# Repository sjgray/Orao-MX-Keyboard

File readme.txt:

Orao 2007 MX Keyboard - By Walter Miraglia and Steve Gray
=====================   Updated: 2026-05-05

This is a mechanical keyboard for the Orao 2007 computer.
It is based on the original keyboard but is slightly modified.

The changes are:

- Larger SHIFT keys.
- Larger ENTER key.
- Relocated cursor/arrow keys with Inverted-T configuration.
- Relocated and re-arranged PF keys.
- 6.25U SPACEBAR, 1.5U ENTER and SHIFT keys.

MX Switches
-----------

This design takes standard MX 3-pin or 5-pin cherry-type switches.
Five-pin switches are recommended for easier alignment.

Keycaps
-------

As this layout is unique I suggest you get blank DSA or XDA keycaps
and use sticker or waterslide sheets to label the keys. There are two
Keycap Sheets; One for Light keycaps (White, Grey,Beige etc) and one
for Black keycaps. The original keyboard was used as a guide and
additional alternate labels are included such as the PF key's actual
functions, longer names for some keys, and alternate cursor arrows.

For Light keycaps I suggest using Water-slide sheets (aka decal sheets).
For Black keycaps you can use full-page sticker sheets.

Connection
----------

For Rev 1 you will need a 16-pin ribbon cable to connect to the computer pcb.
The DIP connector matches the IC socket on the Orao PCB. Rev 2 and 2b can
also use an IDC or straight Dupont connector.

 The Dupont connector can be a 90 degree header installed on either the top
or bottom of the PCB. For Dupont cables you should use the square-pin male
headers on the Orao PCB. For the IDC connecter, I have seen pre-made
IDC to DIP ribbon cables on AliExpress.

History
-------

2026-04-10 - Rev 1 - Prototype. PCB's made. Needs fixes for function keys and SPACEBAR.
2026-04-30 - Rev 2 - Fix for Function key routing, SPACEBAR position, board size reduced. Add IDC and Dupont cable options.
2026-05-02 - Rev 2b- Revert to original size pcb. This revision is recommended for Walter's 3D case design.
2026-05-05 - Add Keycap Sheets

Steve

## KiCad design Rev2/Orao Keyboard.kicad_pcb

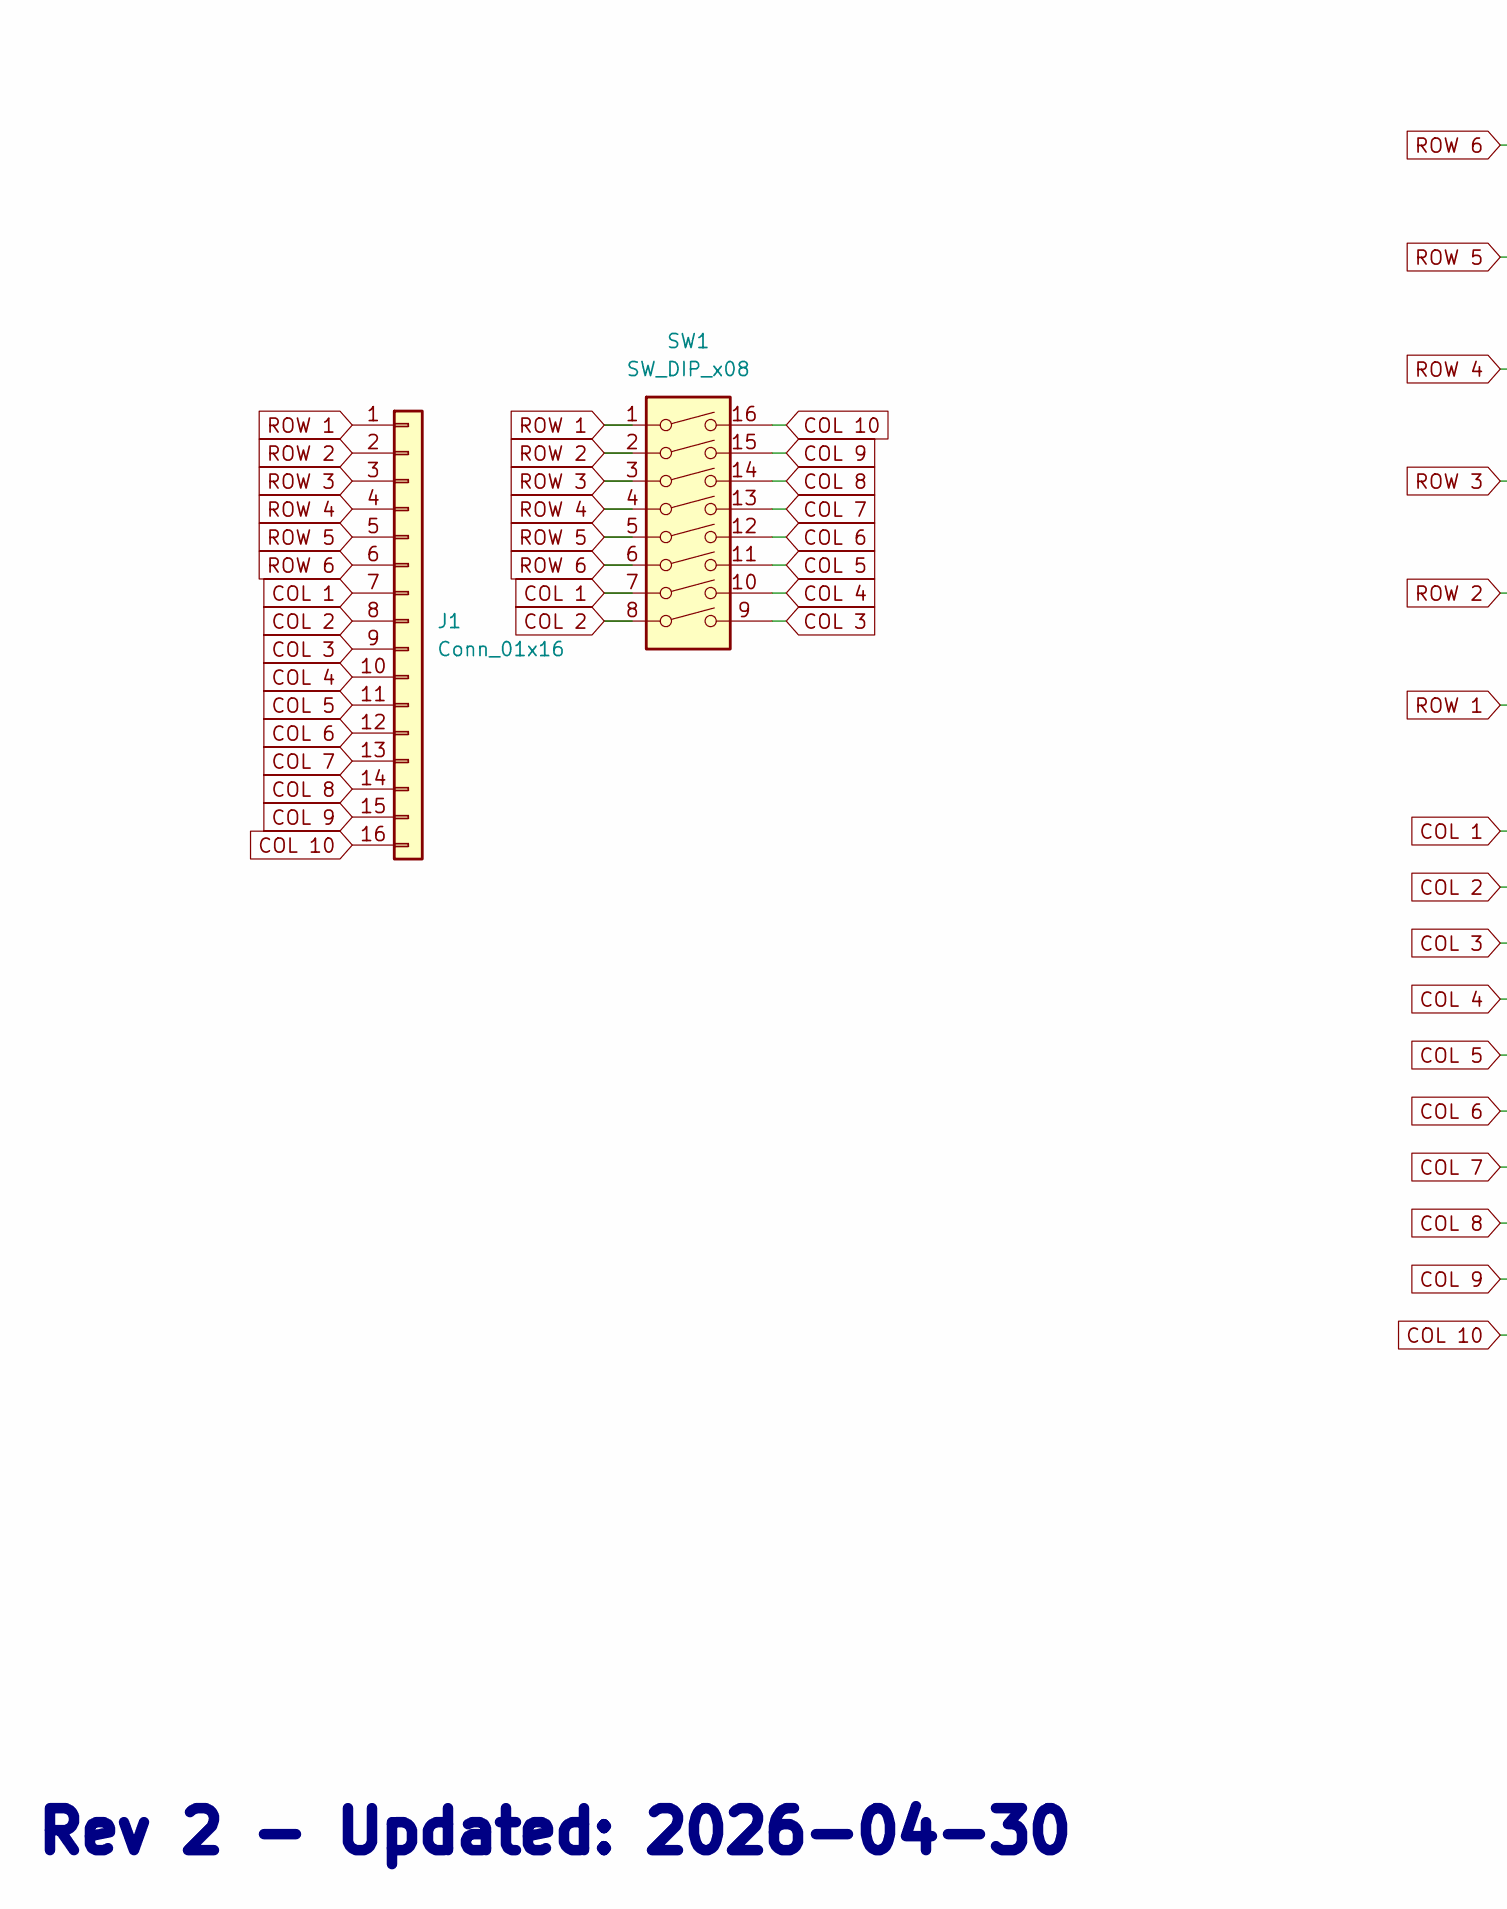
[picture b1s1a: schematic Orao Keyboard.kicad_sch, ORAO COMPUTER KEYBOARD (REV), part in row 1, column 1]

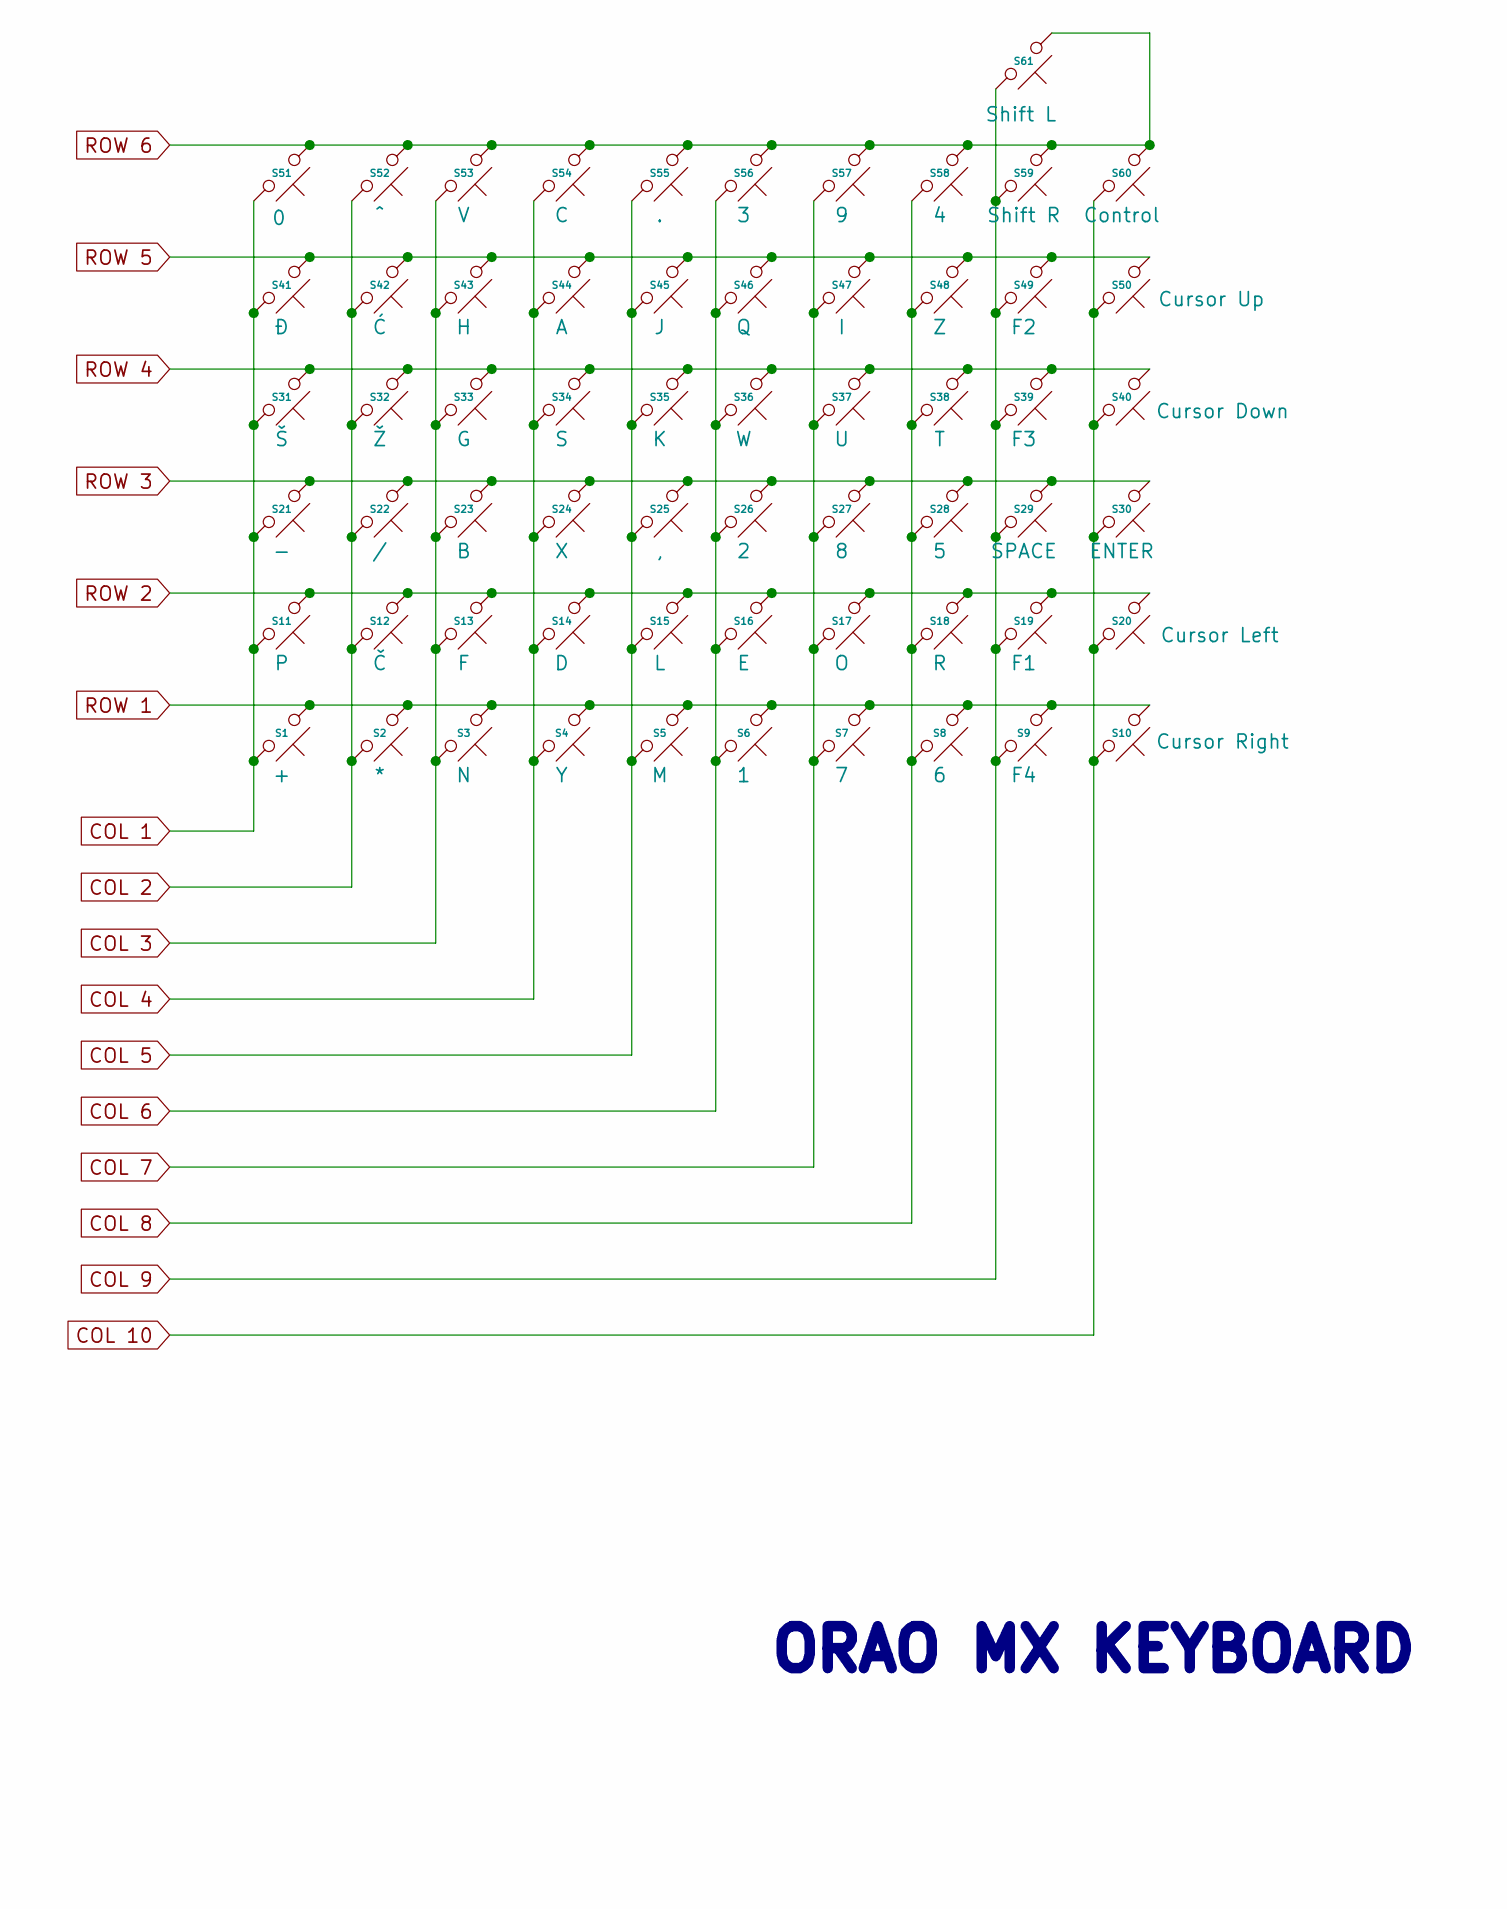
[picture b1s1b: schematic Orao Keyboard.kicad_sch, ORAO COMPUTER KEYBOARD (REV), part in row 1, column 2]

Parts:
J1: Conn_01x16; PinHeader_1x16_P2.54mm_Vertical
S1: +; MX_PCB_1.00u
S2: *; MX_PCB_1.00u
S3: N; MX_PCB_1.00u
S4: Y; MX_PCB_1.00u
S5: M; MX_PCB_1.00u
S6: 1; MX_PCB_1.00u
S7: 7; MX_PCB_1.00u
S8: 6; MX_PCB_1.00u
S9: F4; MX_PCB_1.00u
S10: Cursor Right; MX_PCB_1.00u
S11: P; MX_PCB_1.00u
S12: Č; MX_PCB_1.00u
S13: F; MX_PCB_1.00u
S14: D; MX_PCB_1.00u
S15: L; MX_PCB_1.00u
S16: E; MX_PCB_1.00u
S17: O; MX_PCB_1.00u
S18: R; MX_PCB_1.00u
S19: F1; MX_PCB_1.00u
S20: Cursor Left; MX_PCB_1.00u
S21: -; MX_PCB_1.00u
S22: /; MX_PCB_1.00u
S23: B; MX_PCB_1.00u
S24: X; MX_PCB_1.00u
S25: ,; MX_PCB_1.00u
S26: 2; MX_PCB_1.00u
S27: 8; MX_PCB_1.00u
S28: 5; MX_PCB_1.00u
S29: SPACE; MX_PCB_6.25u
S30: ENTER; MX_PCB_1.50u
S31: Š; MX_PCB_1.00u
S32: Ž; MX_PCB_1.00u
S33: G; MX_PCB_1.00u
S34: S; MX_PCB_1.00u
S35: K; MX_PCB_1.00u
S36: W; MX_PCB_1.00u
S37: U; MX_PCB_1.00u
S38: T; MX_PCB_1.00u
S39: F3; MX_PCB_1.00u
S40: Cursor Down; MX_PCB_1.00u
S41: Đ; MX_PCB_1.00u
S42: Ć; MX_PCB_1.00u
S43: H; MX_PCB_1.00u
S44: A; MX_PCB_1.00u
S45: J; MX_PCB_1.00u
S46: Q; MX_PCB_1.00u
S47: I; MX_PCB_1.00u
S48: Z; MX_PCB_1.00u
S49: F2; MX_PCB_1.00u
S50: Cursor Up; MX_PCB_1.00u
S51: 0; MX_PCB_1.00u
S52: ^; MX_PCB_1.00u
S53: V; MX_PCB_1.00u
S54: C; MX_PCB_1.00u
S55: .; MX_PCB_1.00u
S56: 3; MX_PCB_1.00u
S57: 9; MX_PCB_1.00u
S58: 4; MX_PCB_1.00u
S59: Shift R; MX_PCB_1.50u
S60: Control; MX_PCB_1.00u
S61: Shift L; MX_PCB_1.50u
SW1: SW_DIP_x08; CERDIP-16_W7.62mm_SideBrazed_LongPads

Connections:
COL 1: J1.7, S1.1, S11.1, S21.1, S31.1, S41.1, S51.1, SW1.7
COL 2: J1.8, S2.1, S12.1, S22.1, S32.1, S42.1, S52.1, SW1.8
COL 3: J1.9, S3.1, S13.1, S23.1, S33.1, S43.1, S53.1, SW1.9
COL 4: J1.10, S4.1, S14.1, S24.1, S34.1, S44.1, S54.1, SW1.10
COL 5: J1.11, S5.1, S15.1, S25.1, S35.1, S45.1, S55.1, SW1.11
COL 6: J1.12, S6.1, S16.1, S26.1, S36.1, S46.1, S56.1, SW1.12
COL 7: J1.13, S7.1, S17.1, S27.1, S37.1, S47.1, S57.1, SW1.13
COL 8: J1.14, S8.1, S18.1, S28.1, S38.1, S48.1, S58.1, SW1.14
COL 9: J1.15, S9.1, S19.1, S29.1, S39.1, S49.1, S59.1, S61.1, SW1.15
COL 10: J1.16, S10.1, S20.1, S30.1, S40.1, S50.1, S60.1, SW1.16
ROW 1: J1.1, S1.2, S2.2, S3.2, S4.2, S5.2, S6.2, S7.2, S8.2, S9.2, S10.2, SW1.1
ROW 2: J1.2, S11.2, S12.2, S13.2, S14.2, S15.2, S16.2, S17.2, S18.2, S19.2, S20.2, SW1.2
ROW 3: J1.3, S21.2, S22.2, S23.2, S24.2, S25.2, S26.2, S27.2, S28.2, S29.2, S30.2, SW1.3
ROW 4: J1.4, S31.2, S32.2, S33.2, S34.2, S35.2, S36.2, S37.2, S38.2, S39.2, S40.2, SW1.4
ROW 5: J1.5, S41.2, S42.2, S43.2, S44.2, S45.2, S46.2, S47.2, S48.2, S49.2, S50.2, SW1.5
ROW 6: J1.6, S51.2, S52.2, S53.2, S54.2, S55.2, S56.2, S57.2, S58.2, S59.2, S60.2, S61.2, SW1.6

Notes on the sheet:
ORAO MX KEYBOARD
Rev 2 - Updated: 2026-04-30

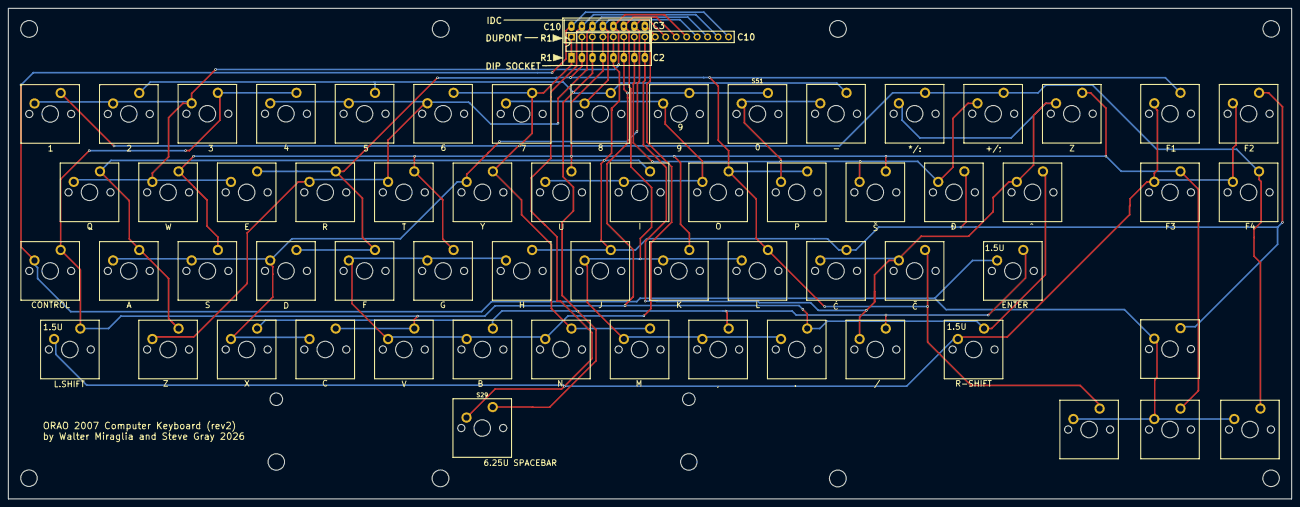
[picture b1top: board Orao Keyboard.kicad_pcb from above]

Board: 2 copper layers, 311.1 x 118.9 mm, 63 parts (0 on the bottom side), 16 nets.

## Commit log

2026-04-12 Initial design
    Initial design. Untested. Please wait until confirmed working before ordering boards!
2026-05-01 Rev 2
    Same layout as Rev 1. Fixes for function keys and SPACEBAR position. Add additional ribbon cable options - IDC and Dupont. Dupont could be a 90 degree connector and mounted on the top or bottom of th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
2026-05-02 Rev 2b
    Reverted to original PCB size.
2026-05-02 Add additional connector info
    Add IDC and Dupont connector info.
2026-05-05 Add Keycap sheets
    One for light keycaps and waterslide sheets, and one for Black keycaps using sticker sheets.
2026-05-05 Now US Letter and A4 page sizes
    Plus renamed the files to be consistent.
